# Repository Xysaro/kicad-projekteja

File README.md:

# kicad-projekteja

sisältää kirjastot

kicad 5

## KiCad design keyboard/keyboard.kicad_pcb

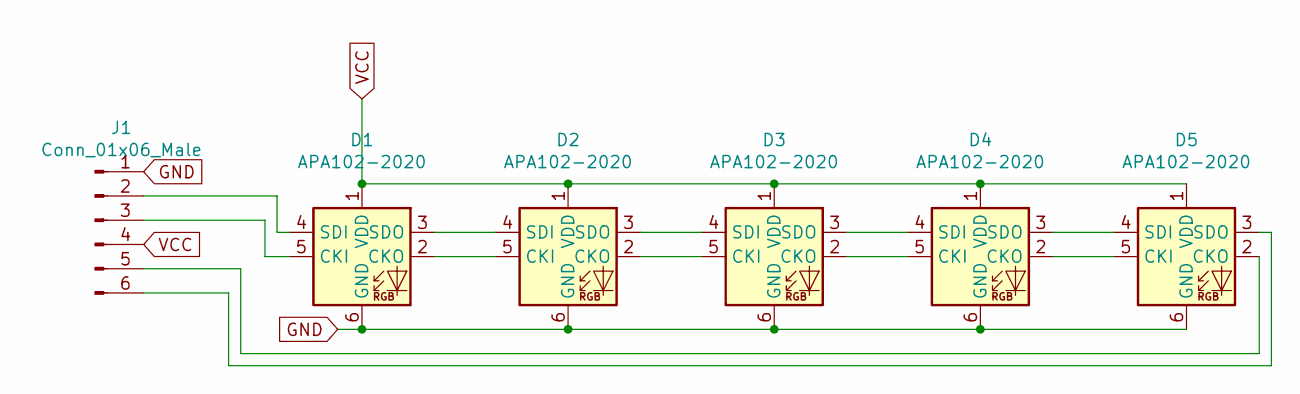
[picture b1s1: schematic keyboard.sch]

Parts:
D1, D2, D3, D4, D5: APA102-2020; LED-APA102-2020
J1: Conn_01x06_Male; PinHeader_1x06_P2.54mm_Vertical

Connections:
GND: D1.6 (GND), D2.6 (GND), D3.6 (GND), D4.6 (GND), D5.6 (GND), J1.1
unnamed: D1.2 (CKO), D2.5 (CKI)
unnamed: D1.3 (SDO), D2.4 (SDI)
unnamed: D1.4 (SDI), J1.2
unnamed: D1.5 (CKI), J1.3
unnamed: D2.2 (CKO), D3.5 (CKI)
unnamed: D2.3 (SDO), D3.4 (SDI)
unnamed: D3.2 (CKO), D4.5 (CKI)
unnamed: D3.3 (SDO), D4.4 (SDI)
unnamed: D4.2 (CKO), D5.5 (CKI)
unnamed: D4.3 (SDO), D5.4 (SDI)
unnamed: D5.2 (CKO), J1.5
unnamed: D5.3 (SDO), J1.6
VCC: D1.1 (VDD), D2.1 (VDD), D3.1 (VDD), D4.1 (VDD), D5.1 (VDD), J1.4

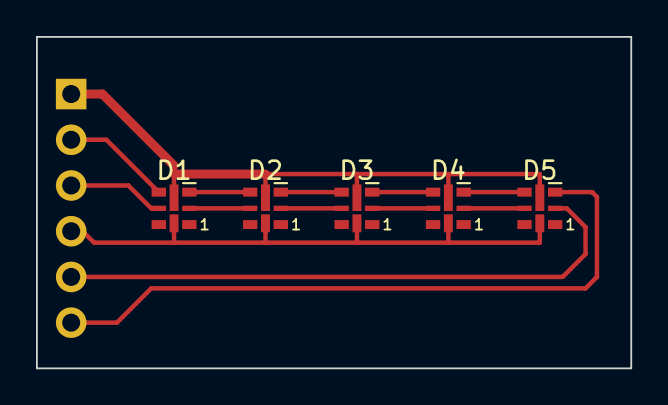
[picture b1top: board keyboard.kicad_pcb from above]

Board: 2 copper layers, 33.0 x 18.4 mm, 6 parts (1 on the bottom side), 14 nets.

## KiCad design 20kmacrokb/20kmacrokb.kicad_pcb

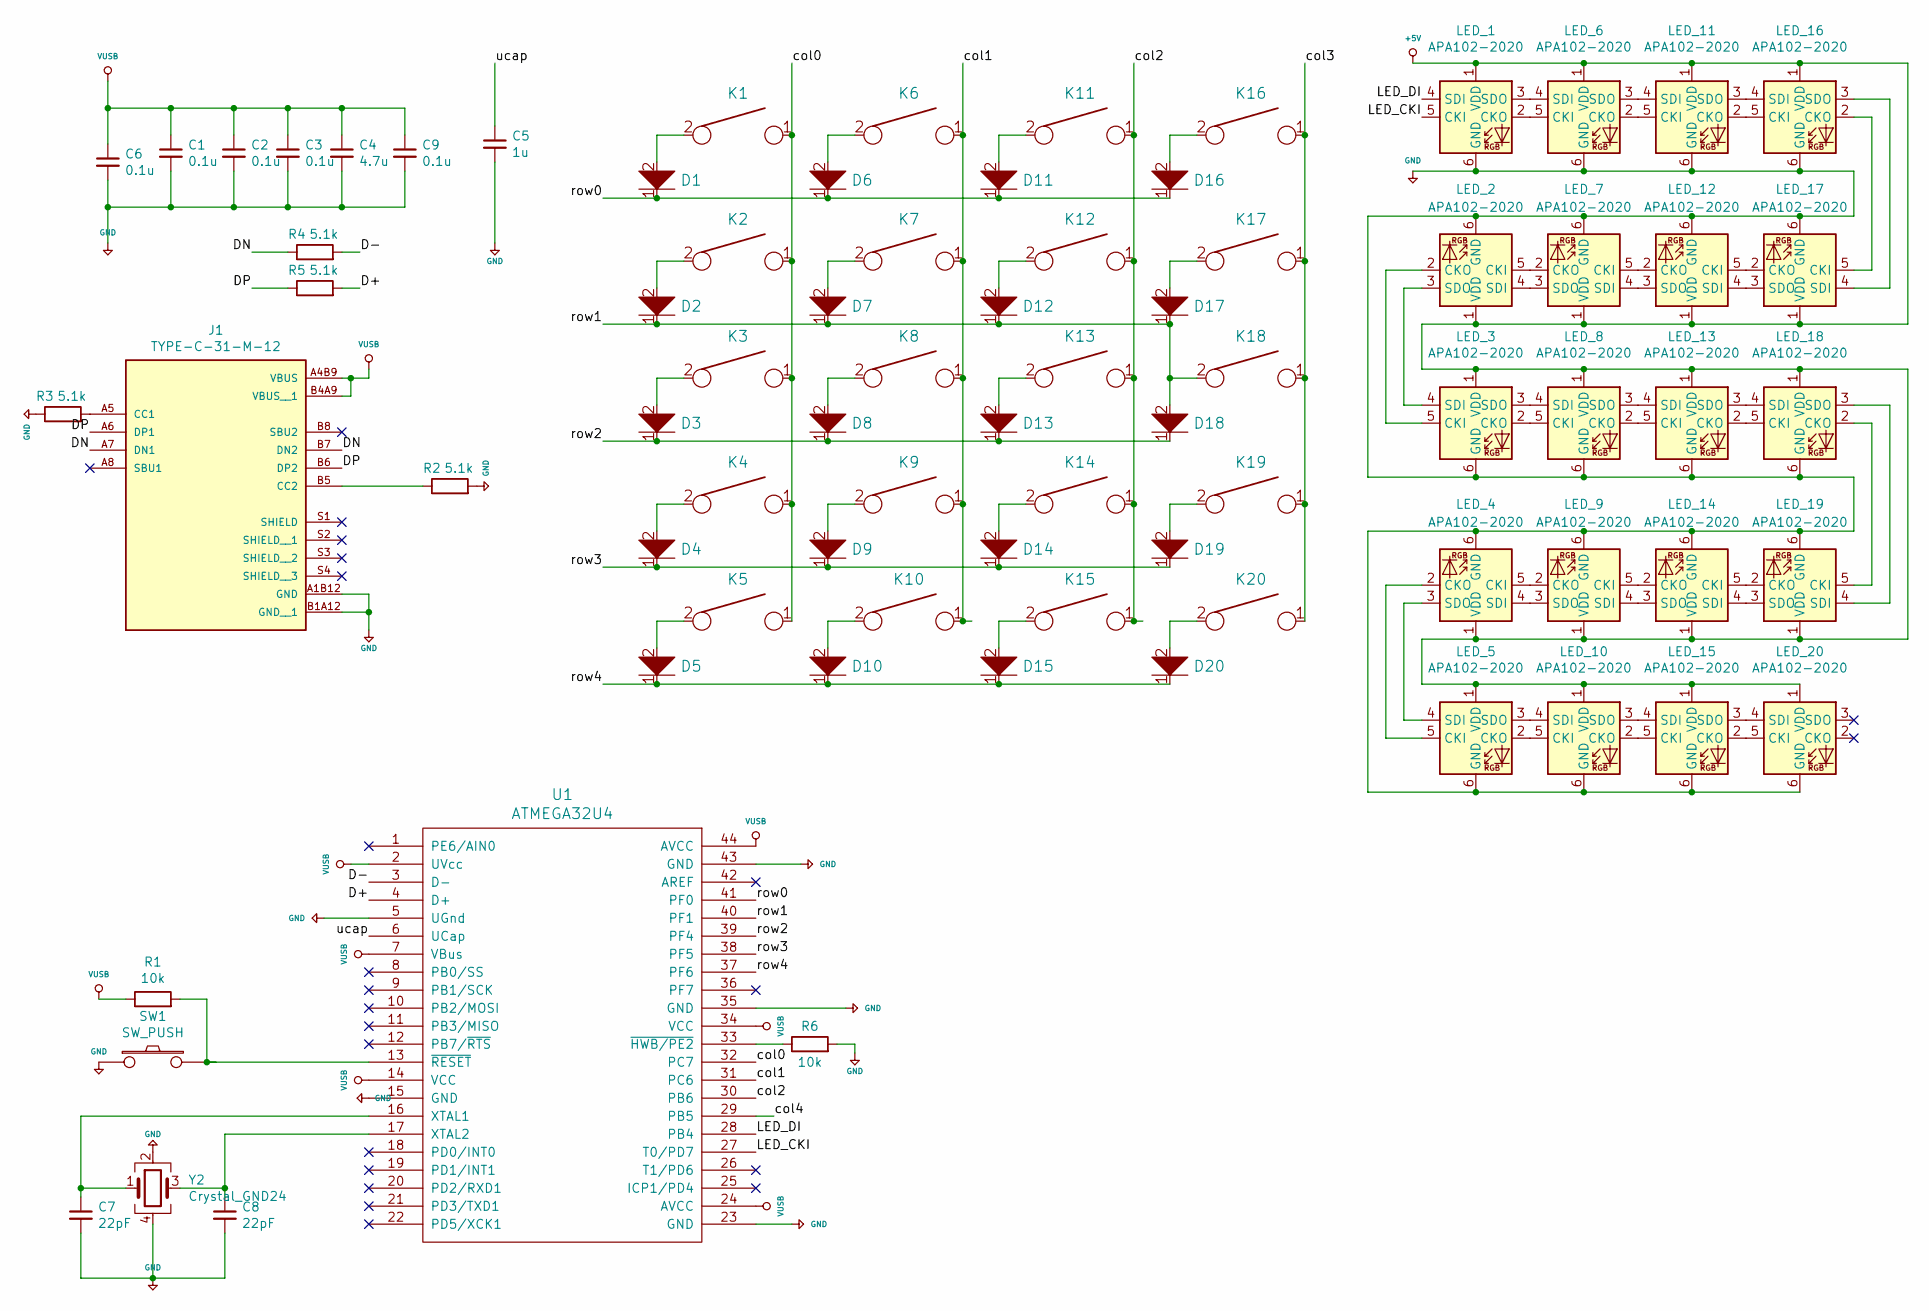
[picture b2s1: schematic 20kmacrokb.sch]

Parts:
C1, C2, C3, C6, C9: 0.1u; C_0805_2012Metric_Pad1.18x1.45mm_HandSolder
C4: 4.7u; C_0805_2012Metric_Pad1.18x1.45mm_HandSolder
C5: 1u; C_0805_2012Metric_Pad1.18x1.45mm_HandSolder
C7, C8: 22pF; C_0805_2012Metric_Pad1.18x1.45mm_HandSolder
D1, D2, D3, D4, D5, D6, D7, D8, D9, D10, D11, D12, D13, D14, D15, D16, D17, D18, D19, D20: D; D_SOD123
J1: TYPE-C-31-M-12; HRO_TYPE-C-31-M-12; PARTREV A
K1, K2, K3, K4, K5, K6, K7, K8, K9, K10, K11, K12, K13, K14, K15, K16, K17, K18, K19, K20: KEYSW; Kailh_socket_MX
LED_1, LED_2, LED_3, LED_4, LED_5, LED_6, LED_7, LED_8, LED_9, LED_10, LED_11, LED_12, LED_13, LED_14, LED_15, LED_16, LED_17, LED_18, LED_19, LED_20: APA102-2020; LED-APA102-2020
R1, R6: 10k; R_0805_2012Metric_Pad1.20x1.40mm_HandSolder
R2, R3, R4, R5: 5.1k; R_0805_2012Metric_Pad1.20x1.40mm_HandSolder
SW1: SW_PUSH; SW_SPST_TL3342
U1: ATMEGA32U4; QFP44_reflow
Y2: Crystal_GND24; Crystal_SMD_SeikoEpson_FA238-4Pin_3.2x2.5mm_HandSoldering

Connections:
/D+: R5.2, U1.4 (D+)
/D-: R4.2, U1.3 (D-)
/DN: J1.A7 (DN1), J1.B7 (DN2), R4.1
/DP: J1.A6 (DP1), J1.B6 (DP2), R5.1
/LED_CKI: LED_1.5 (CKI), U1.27 (T0/PD7)
/LED_DI: LED_1.4 (SDI), U1.28 (PB4)
/col0: K1.1, K2.1, K3.1, K4.1, K5.1, U1.32 (PC7)
/col1: K6.1, K7.1, K8.1, K9.1, K10.1, U1.31 (PC6)
/col2: K11.1, K12.1, K13.1, K14.1, K15.1, U1.30 (PB6)
/col3: K16.1, K17.1, K18.1, K19.1, K20.1
/col4: U1.29 (PB5)
/row0: D1.1, D6.1, D11.1, D16.1, U1.41 (PF0)
/row1: D2.1, D7.1, D12.1, D17.1, D18.2, K18.2, U1.40 (PF1)
/row2: D3.1, D8.1, D13.1, D18.1, U1.39 (PF4)
/row3: D4.1, D9.1, D14.1, D19.1, U1.38 (PF5)
/row4: D5.1, D10.1, D15.1, D20.1, U1.37 (PF6)
/ucap: C5.1, U1.6 (UCap)
unnamed: C7.1, U1.16 (XTAL1), Y2.1
unnamed: C8.1, U1.17 (XTAL2), Y2.3
unnamed: D1.2, K1.2
unnamed: D2.2, K2.2
unnamed: D3.2, K3.2
unnamed: D4.2, K4.2
unnamed: D5.2, K5.2
unnamed: D6.2, K6.2
unnamed: D7.2, K7.2
unnamed: D8.2, K8.2
unnamed: D9.2, K9.2
unnamed: D10.2, K10.2
unnamed: D11.2, K11.2
unnamed: D12.2, K12.2
unnamed: D13.2, K13.2
unnamed: D14.2, K14.2
unnamed: D15.2, K15.2
unnamed: D16.2, K16.2
unnamed: D17.2, K17.2
unnamed: D19.2, K19.2
unnamed: D20.2, K20.2
unnamed: J1.A5 (CC1), R3.2
unnamed: J1.B5 (CC2), R2.1
unnamed: LED_1.2 (CKO), LED_6.5 (CKI)
unnamed: LED_1.3 (SDO), LED_6.4 (SDI)
unnamed: LED_2.2 (CKO), LED_3.5 (CKI)
unnamed: LED_2.3 (SDO), LED_3.4 (SDI)
unnamed: LED_2.4 (SDI), LED_7.3 (SDO)
unnamed: LED_2.5 (CKI), LED_7.2 (CKO)
unnamed: LED_3.2 (CKO), LED_8.5 (CKI)
unnamed: LED_3.3 (SDO), LED_8.4 (SDI)
unnamed: LED_4.2 (CKO), LED_5.5 (CKI)
unnamed: LED_4.3 (SDO), LED_5.4 (SDI)
unnamed: LED_4.4 (SDI), LED_9.3 (SDO)
unnamed: LED_4.5 (CKI), LED_9.2 (CKO)
unnamed: LED_10.2 (CKO), LED_15.5 (CKI)
unnamed: LED_10.3 (SDO), LED_15.4 (SDI)
unnamed: LED_5.3 (SDO), LED_10.4 (SDI)
unnamed: LED_5.2 (CKO), LED_10.5 (CKI)
unnamed: LED_11.2 (CKO), LED_16.5 (CKI)
unnamed: LED_11.3 (SDO), LED_16.4 (SDI)
unnamed: LED_6.3 (SDO), LED_11.4 (SDI)
unnamed: LED_6.2 (CKO), LED_11.5 (CKI)
unnamed: LED_7.5 (CKI), LED_12.2 (CKO)
unnamed: LED_7.4 (SDI), LED_12.3 (SDO)
unnamed: LED_12.4 (SDI), LED_17.3 (SDO)
unnamed: LED_12.5 (CKI), LED_17.2 (CKO)
unnamed: LED_13.2 (CKO), LED_18.5 (CKI)
unnamed: LED_13.3 (SDO), LED_18.4 (SDI)
unnamed: LED_8.3 (SDO), LED_13.4 (SDI)
unnamed: LED_8.2 (CKO), LED_13.5 (CKI)
unnamed: LED_9.5 (CKI), LED_14.2 (CKO)
unnamed: LED_9.4 (SDI), LED_14.3 (SDO)
unnamed: LED_14.4 (SDI), LED_19.3 (SDO)
unnamed: LED_14.5 (CKI), LED_19.2 (CKO)
unnamed: LED_15.2 (CKO), LED_20.5 (CKI)
unnamed: LED_15.3 (SDO), LED_20.4 (SDI)
unnamed: LED_16.2 (CKO), LED_17.5 (CKI)
unnamed: LED_16.3 (SDO), LED_17.4 (SDI)
unnamed: LED_18.2 (CKO), LED_19.5 (CKI)
unnamed: LED_18.3 (SDO), LED_19.4 (SDI)
unnamed: R1.2, SW1.2, U1.13 (~RESET)
unnamed: R6.1, U1.33 (~HWB/PE2)
VUSB: C1.1, C2.1, C3.1, C4.1, C6.1, C9.1, J1.A4B9 (VBUS), J1.B4A9 (VBUS__1), R1.1, U1.2 (UVcc), U1.7 (VBus), U1.14 (VCC), U1.24 (AVCC), U1.34 (VCC), U1.44 (AVCC)

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
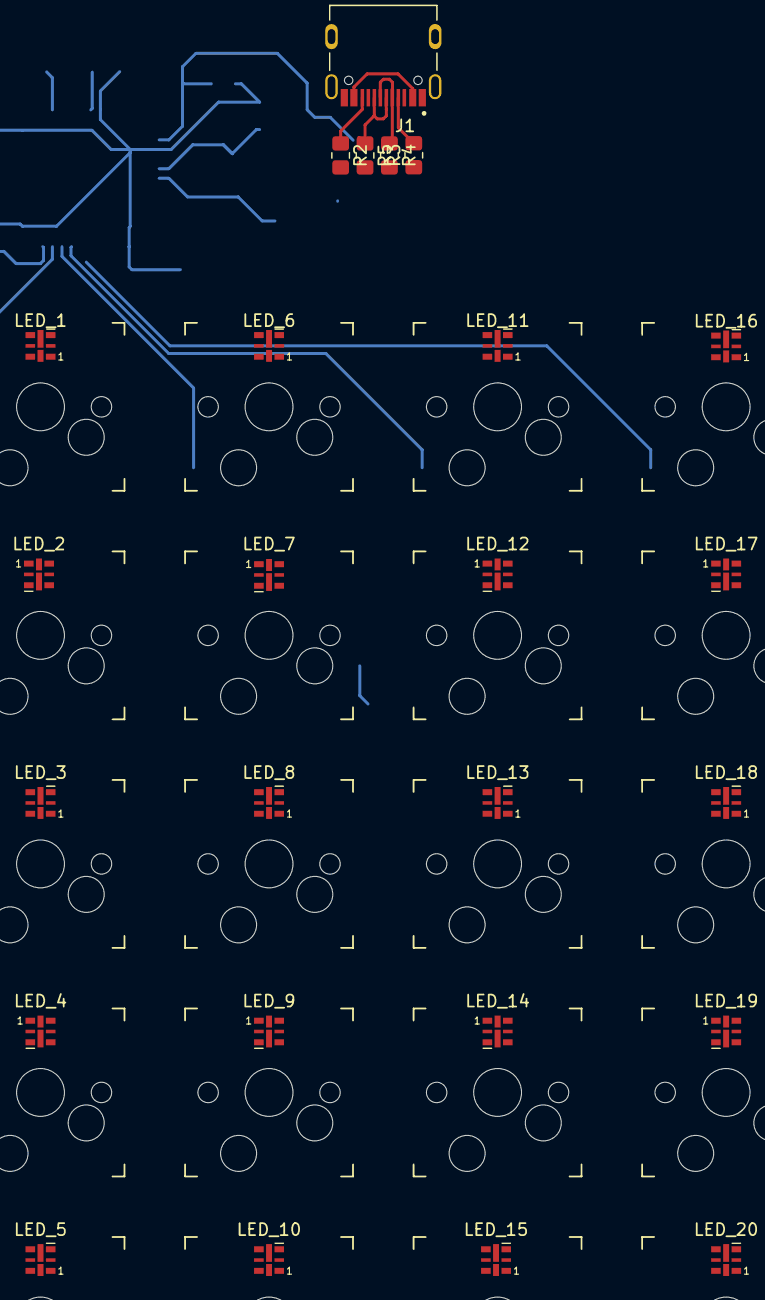
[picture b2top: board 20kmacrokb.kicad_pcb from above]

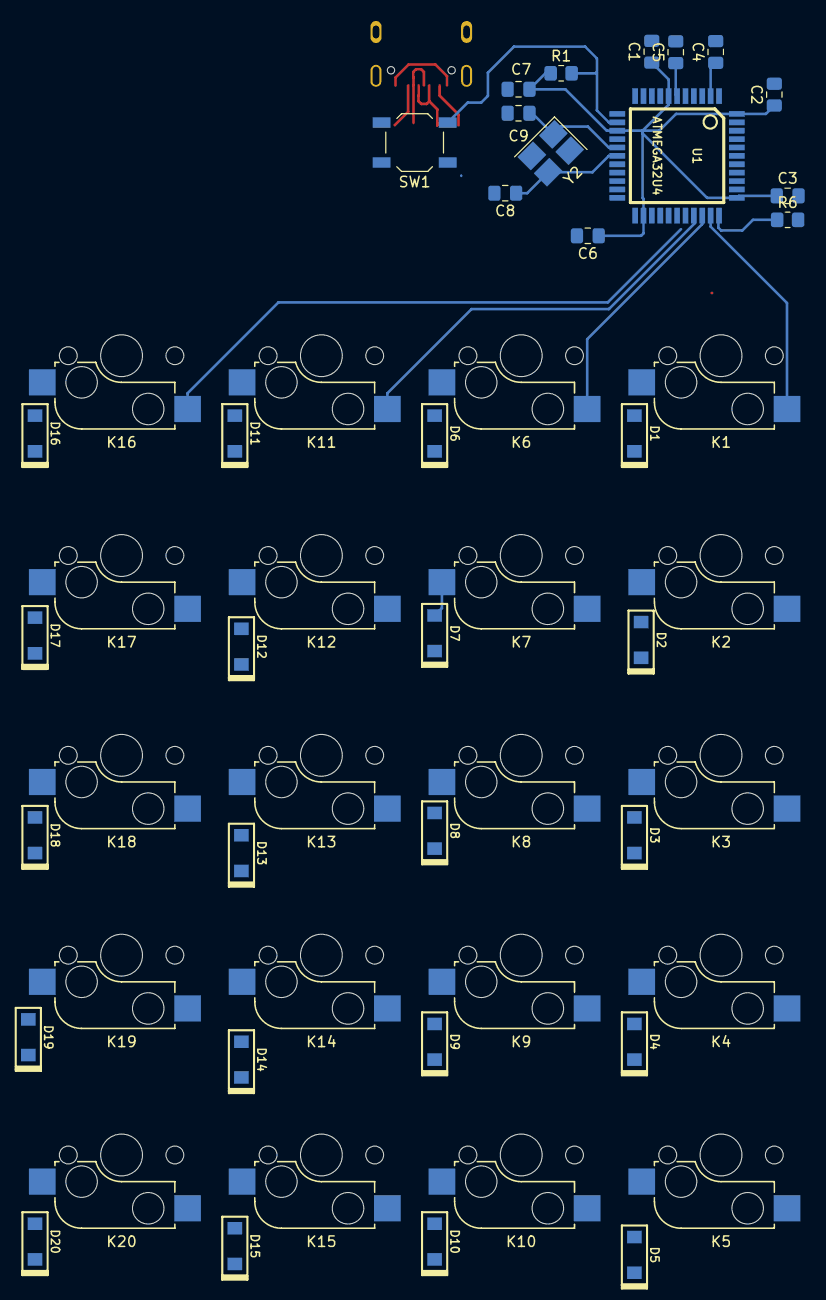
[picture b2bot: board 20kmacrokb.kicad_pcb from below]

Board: 2 copper layers, 79 parts (34 on the bottom side), 81 nets.

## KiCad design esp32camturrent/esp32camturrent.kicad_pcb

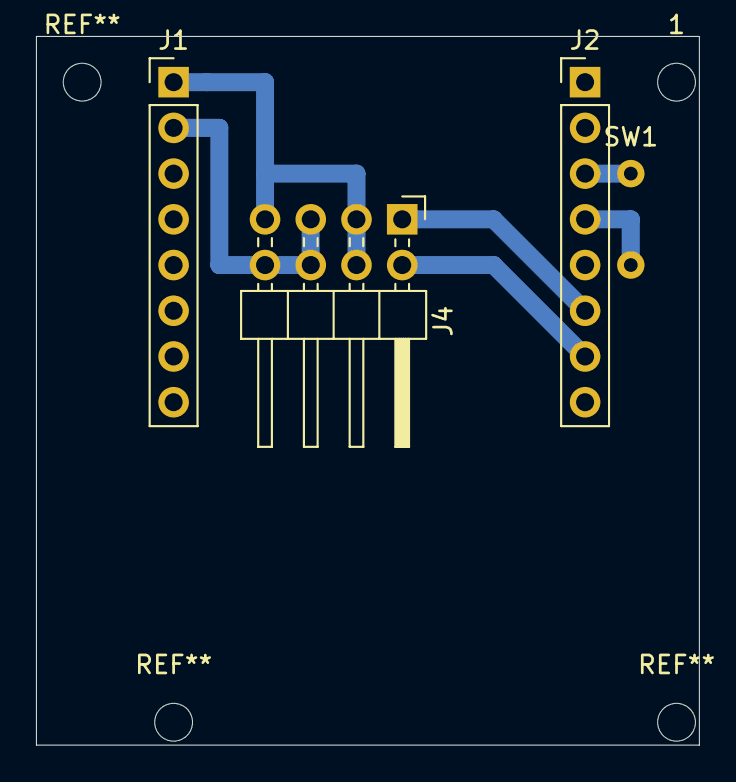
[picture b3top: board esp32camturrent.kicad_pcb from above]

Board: 2 copper layers, 36.8 x 39.4 mm, 5 parts (0 on the bottom side), 5 nets.

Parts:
1: MountingHole_2.1mm
J1, J2: Conn_01x08; PinHeader_1x08_P2.54mm_Vertical
J4: Conn_02x04_Odd_Even; PinHeader_2x04_P2.54mm_Horizontal
SW1: SW_Push; tactile_switch

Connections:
+5V: J1.1, J4.3, J4.4, J4.7
GND: J1.2, J2.4, J4.5, J4.6, J4.8, SW1.2
I00: J2.3, SW1.1
U0R: J2.6, J4.1
U0T: J2.7, J4.2

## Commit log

2021-09-17 first
2021-09-17 all files
